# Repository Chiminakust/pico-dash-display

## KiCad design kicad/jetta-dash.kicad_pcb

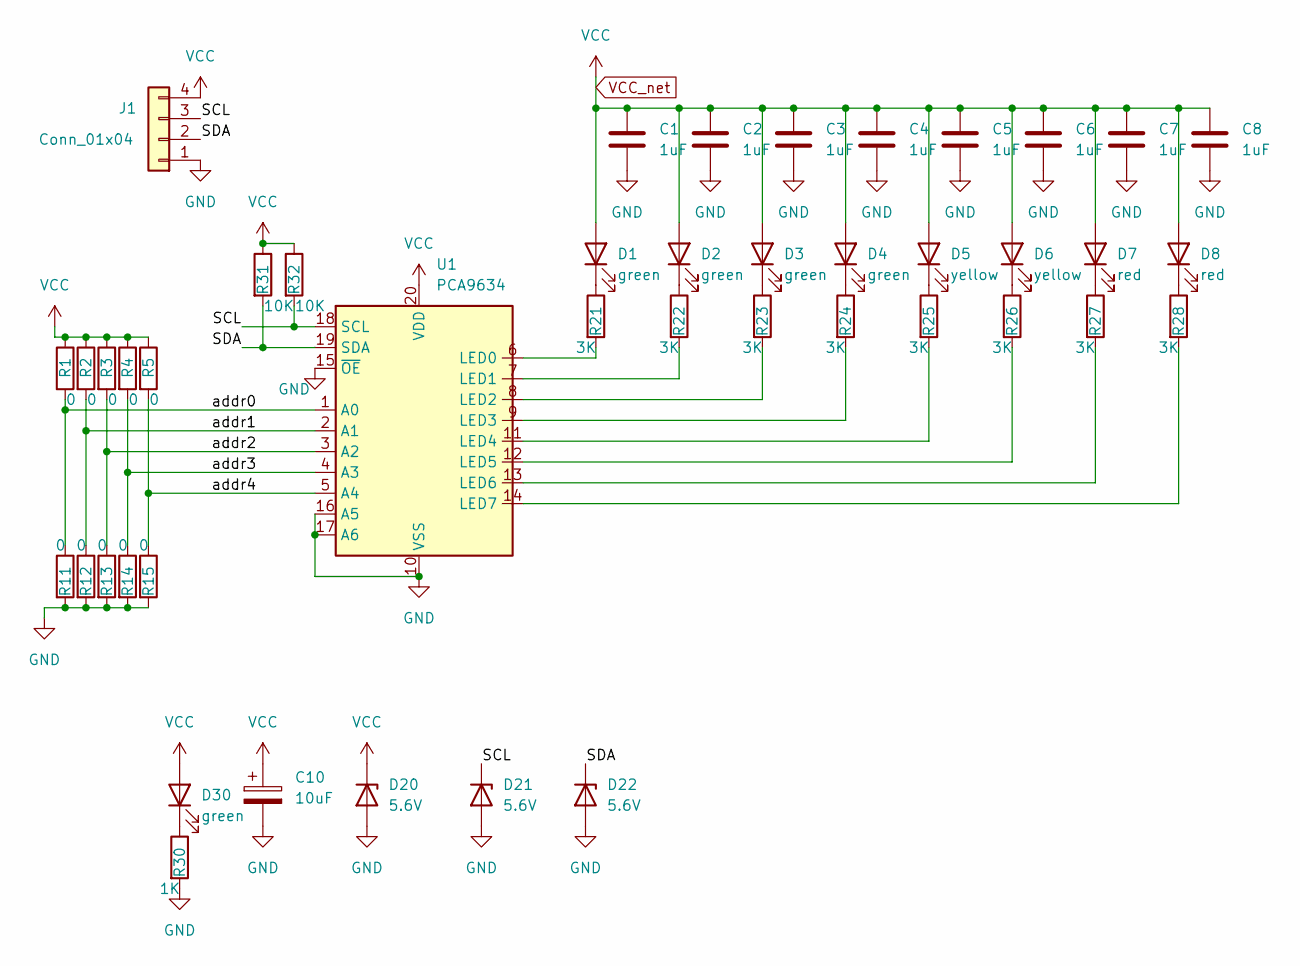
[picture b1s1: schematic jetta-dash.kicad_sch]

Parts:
C1, C2, C3, C4, C5, C6, C7, C8: 1uF; C_0805_2012Metric
C10: 10uF; C_Elec_6.3x5.4
D1, D2, D3, D4, D30: green; LED_0805_2012Metric
D5, D6: yellow; LED_0805_2012Metric
D7, D8: red; LED_0805_2012Metric
D20, D21, D22: 5.6V; D_0402_1005Metric_Pad0.77x0.64mm_HandSolder
J1: Conn_01x04; PinHeader_1x04_P2.54mm_Vertical
R1, R2, R3, R4, R5, R11, R12, R13, R14, R15: 0; R_0402_1005Metric
R21, R22, R23, R24, R25, R26, R27, R28: 3K; R_0805_2012Metric
R30: 1K; R_0805_2012Metric
R31, R32: 10K; R_Axial_DIN0207_L6.3mm_D2.5mm_P7.62mm_Horizontal
U1: PCA9634; SOIC-20W_7.5x12.8mm_P1.27mm

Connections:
/SCL: D21.1 (K), J1.3, R32.2, U1.18 (SCL)
/SDA: D22.1 (K), J1.2, R31.2, U1.19 (SDA)
/addr0: R1.2, R11.1, U1.1 (A0)
/addr1: R2.2, R12.1, U1.2 (A1)
/addr2: R3.2, R13.1, U1.3 (A2)
/addr3: R4.2, R14.1, U1.4 (A3)
/addr4: R5.2, R15.1, U1.5 (A4)
GND: C1.2, C2.2, C3.2, C4.2, C5.2, C6.2, C7.2, C8.2, C10.2, D20.2 (A), D21.2 (A), D22.2 (A), J1.1, R11.2, R12.2, R13.2, R14.2, R15.2, R30.2, U1.10 (VSS), U1.15 (~OE), U1.16 (A5), U1.17 (A6); also elsewhere on the board
unnamed: D1.1 (K), R21.1
unnamed: D2.1 (K), R22.1
unnamed: D3.1 (K), R23.1
unnamed: D4.1 (K), R24.1
unnamed: D5.1 (K), R25.1
unnamed: D6.1 (K), R26.1
unnamed: D7.1 (K), R27.1
unnamed: D8.1 (K), R28.1
unnamed: D30.1 (K), R30.1
unnamed: R21.2, U1.6 (LED0)
unnamed: R22.2, U1.7 (LED1)
unnamed: R23.2, U1.8 (LED2)
unnamed: R24.2, U1.9 (LED3)
unnamed: R25.2, U1.11 (LED4)
unnamed: R26.2, U1.12 (LED5)
unnamed: R27.2, U1.13 (LED6)
unnamed: R28.2, U1.14 (LED7)
VCC_net: C1.1, C2.1, C3.1, C4.1, C5.1, C6.1, C7.1, C8.1, C10.1, D1.2 (A), D2.2 (A), D3.2 (A), D4.2 (A), D5.2 (A), D6.2 (A), D7.2 (A), D8.2 (A), D20.1 (K), D30.2 (A), J1.4, R1.1, R2.1, R3.1, R4.1, R5.1, R31.1, R32.1, U1.20 (VDD)

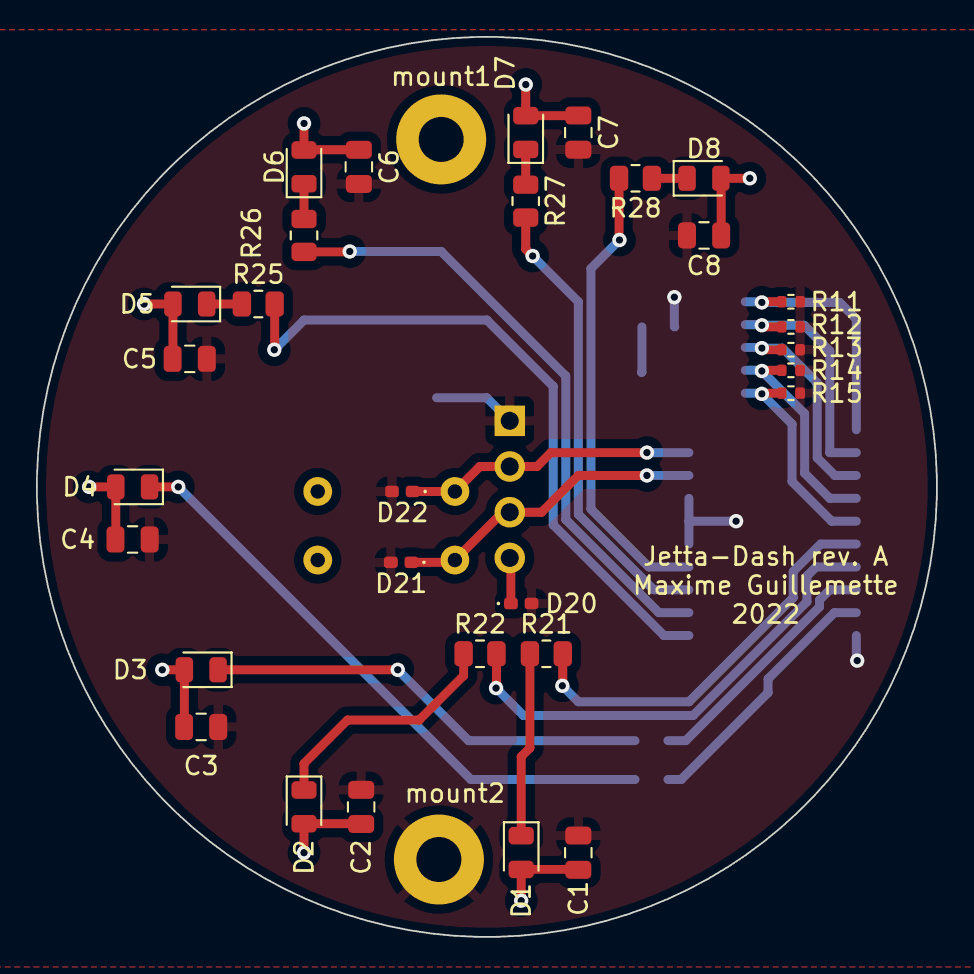
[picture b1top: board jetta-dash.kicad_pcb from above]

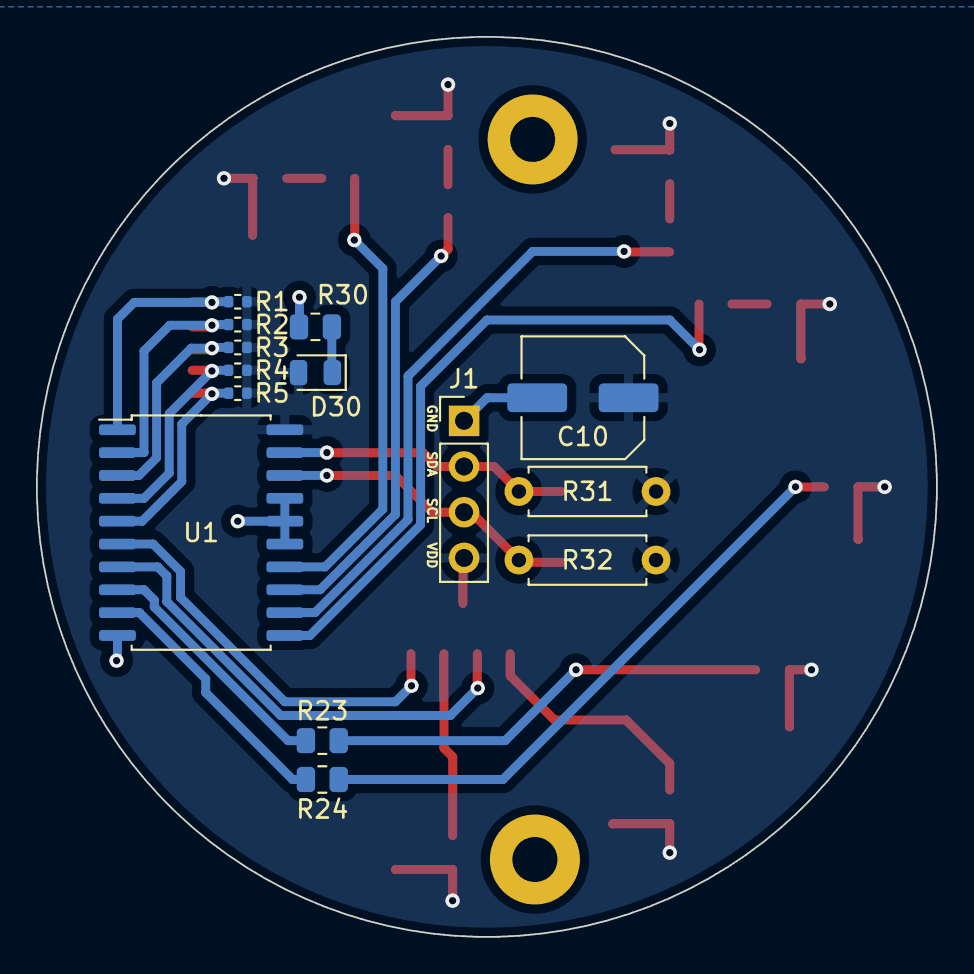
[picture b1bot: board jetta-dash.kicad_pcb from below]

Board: 2 copper layers, 50.0 x 50.0 mm, 46 parts (14 on the bottom side), 26 nets.

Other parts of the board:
mount1, mount2: MountingHole_2.5mm_Pad

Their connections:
GND: mount2.1; also elsewhere on the board

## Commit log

2021-12-30 trying to get the original pyobd to play nice with the pico's memory
2021-12-30 probably need pint for this to work and I get weird TypeErrors without an error string. I give up for now and will try to follow the elm327 datasheet and make my own module
2021-12-30 trying to make elm327.py from scratch, can't be *that* hard, right?
2021-12-30 added commands I want to use
2022-01-22 works for 1 display
2022-04-12 added PCA9634 driver
2022-04-12 improved resilience of elm327 and main now tests the new PCA chip
2022-05-17 backup
2022-06-05 updated S7S to have a method to change i2c address
2022-06-06 changed gauge to use PCA9634
2022-06-06 updated pca9634, works as intended with my pcb
2022-06-06 updated main to use new gauge with pcb and added print on OSError in s7s (now mostly fixed using 1K pull up resistors on the I2C of the sparkfun S7S module
2022-06-11 updated all modules, integrated with 3 gauges on real hardware with the ELM327 and it works
2022-07-26 added hardware
2022-07-27 Create LICENSE
